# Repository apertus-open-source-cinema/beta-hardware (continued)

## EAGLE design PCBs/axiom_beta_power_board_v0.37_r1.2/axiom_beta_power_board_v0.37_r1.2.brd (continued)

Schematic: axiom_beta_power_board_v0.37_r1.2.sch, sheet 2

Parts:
BETA: µZ-FCI-SOCKET-NOHOLES-R; µZ-SOCKET-NOHOLES-R
FID1, FID2, FID3, FID4: FIDUCIAL; FID_ARROW
JX1T, JX2T: BERGSTAK-61082; 61082

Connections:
BANK13_SE_0: BETA.200 (_0); also elsewhere on the board
CSO_NE_V: BETA.7 (FPGA_VBAT); also elsewhere on the board
CSO_SW_V: BETA.112 (VIN_HDR); also elsewhere on the board
GND: BETA.15 (GND), BETA.16 (GND), BETA.21 (GND), BETA.22 (GND), BETA.27 (GND), BETA.28 (GND), BETA.33 (GND), BETA.34 (GND), BETA.39 (GND), BETA.40 (GND), BETA.45 (GND), BETA.46 (GND), BETA.51 (GND), BETA.52 (GND), BETA.65 (GND), BETA.66 (GND), BETA.71 (GND), BETA.72 (GND), BETA.77 (GND), BETA.85 (GND), BETA.86 (GND), BETA.95 (GND), BETA.96 (GND), BETA.115 (GND), BETA.116 (GND), BETA.121 (GND), BETA.122 (GND), BETA.127 (GND), BETA.128 (GND), BETA.133 (GND), BETA.134 (GND), BETA.139 (GND), BETA.140 (GND), BETA.145 (GND), BETA.146 (GND), BETA.151 (GND), BETA.152 (GND), BETA.165 (GND), BETA.166 (GND), BETA.171 (GND), BETA.172 (GND), BETA.177 (GND), BETA.185 (GND), BETA.186 (GND), BETA.191 (GND), BETA.192 (GND); also elsewhere on the board
NC$1: BETA.113 (_0)
NC$2: BETA.114 (_1)
PCIE_I2C_V: BETA.198 (VCCO_13)
PCIE_N_5V: BETA.59 (VIN_HDR), BETA.60 (VIN_HDR)
PCIE_N_V: BETA.79 (VCCO_34), BETA.80 (VCCO_34); also elsewhere on the board
PCIE_N_VCCIO: BETA.78 (VCCO_34)
PCIE_S_5V: BETA.159 (VIN_HDR), BETA.160 (VIN_HDR)
PCIE_S_V: BETA.179 (VCCO_35), BETA.180 (VCCO_35); also elsewhere on the board
PCIE_S_VCCIO: BETA.178 (VCCO_35)
PEX_N_V: BETA.57 (VIN_HDR), BETA.58 (VIN_HDR)
PEX_S_V: BETA.157 (VIN_HDR), BETA.158 (VIN_HDR)
SE_0: BETA.9 (_0); also elsewhere on the board
SE_1: BETA.10 (_1); also elsewhere on the board

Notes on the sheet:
AXIOM Beta Power Board
Copyright (C) 2014-2020 H.Poetzl Licensed under CERN OHL v.1.2
Beta Main Board Power [Top]

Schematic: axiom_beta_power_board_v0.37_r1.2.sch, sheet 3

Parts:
BETA: µZ-FCI-SOCKET-NOHOLES-R; µZ-SOCKET-NOHOLES-R
C1, C5, C6, C10: 10u; 0603-B
C2, C4, C7, C9: 10u; 1206-C
C3, C8: 1n; 0402-C
C83, C84: 10u; 0603-C
C93: 4u7; 0402-B
D1: PMEG2010BELD; DFN1006D-2
L18: L0603-C; 0603-C
Q1: NX3008NBKT; SOT416
R110: 523k; 0402-C
R111, R115, R118: 100k; 0402-C
R112: 180k; 0402-B
R113: 20k; 0402-B
R114: 536k; 0402-C
R116, R117: 100k; 0402-B
R126: 10k; 0402-B
R127, R129: 180k; 0402-C
R128, R130: 20k; 0402-C
S/N: 91658; 3X2MM
U1: PIC16F15325-JQ; UQFN65P400X400X100-17N
U2, U3: TPS82130SIL-GM; SIL0008D-GM
U26: SC202A; MLPQ-13
U31: NCP715; DFN150X150X50-6N
X2: PINHD-2X02_2.54-90°; 2X02/90
ZED: µZ-FCI-CONONLY; µZ-CONONLY

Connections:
!X_MCLR: R126.2, U1.3 (RA3); also elsewhere on the board
BETA_5V: C4.1, C5.1, D1.A, R110.1, U3.4 (VOUT), U3.5 (VOUT); also elsewhere on the board
BETA_5V': C83.1, U26.5 (CTL3), U26.6 (CTL0), U26.7 (CTL1), U26.8 (CTL2), U26.9 (VIN); also elsewhere on the board
BETA_5V_EN: R116.2, U1.8 (RC1), U3.1 (EN)
BETA_5V_PG: U1.1 (RA5), U3.7 (PG)
BETA_TCK: BETA.1 (TCK)
BETA_TDI: BETA.4 (TDI)
BETA_TDO: BETA.3 (TDO)
BETA_TMS: BETA.2 (TMS)
BTN: R127.1, X2.1
BTN_SENSE: R127.2, R128.1, U1.6 (RC3)
FAN: Q1.3 (D), X2.3
FAN_PWM: R118.2, U1.4 (RC5)
GND: C1.2, C2.2, C3.2, C4.2, C5.2, C6.2, C7.2, C8.2, C9.2, C10.2, C83.2, C84.2, C93.2, Q1.2 (S), R111.2, R113.2, R115.2, R128.2, R130.2, S/N.1, U1.13 (GND), U1.EP (GND), U2.3 (GND), U2.EPAD (GND), U3.3 (GND), U3.EPAD (GND), U26.10 (GND), U31.3 (GND), X2.4; also elsewhere on the board
unnamed: C8.1, U2.8 (SS/TR)
unnamed: C3.1, U3.8 (SS/TR)
unnamed: Q1.1 (G), R118.1
unnamed: R110.2, R111.1, U3.6 (FB)
unnamed: R114.2, R115.1, U2.6 (FB)
REGOUT: C84.1, L18.1, U26.4 (SNS), U26.11 (VOUT), U26.12 (VOUT), U26.13 (VOUT)
SN_SENSE: S/N.2, U1.10 (RA2)
VCC: L18.2, R116.1, R117.1, R129.1; also elsewhere on the board
VCC_SENSE: R129.2, R130.1, U1.7 (RC2)
VIN: C1.1, C2.1, C6.1, C7.1, D1.C (K), R112.1, U2.2 (VIN), U3.2 (VIN), U31.1 (IN), X2.2
VIN_SENSE: R112.2, R113.1, U1.9 (RC0)
VSB: C93.1, R126.1, U1.16 (VCC), U31.6 (OUT); also elsewhere on the board
X_SCL: U1.11 (RA1); also elsewhere on the board
X_SDA: U1.12 (RA0); also elsewhere on the board
ZED_5V: C9.1, C10.1, R114.1, U2.4 (VOUT), U2.5 (VOUT); also elsewhere on the board
ZED_5V_EN: R117.2, U1.5 (RC4), U2.1 (EN)
ZED_5V_PG: U1.2 (RA4), U2.7 (PG)
ZED_TCK: ZED.1 (TCK)
ZED_TDI: ZED.4 (TDI)
ZED_TDO: ZED.3 (TDO)
ZED_TMS: ZED.2 (TMS)

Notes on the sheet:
AXIOM Beta Power Board
Copyright (C) 2014-2020 H.Poetzl Licensed under CERN OHL v.1.2
Power Conversion and JTAG

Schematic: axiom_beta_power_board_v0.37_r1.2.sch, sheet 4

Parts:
BETA: µZ-FCI-SOCKET-NOHOLES-R; µZ-SOCKET-NOHOLES-R
ZED: µZ-FCI-CONONLY; µZ-CONONLY

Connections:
BANK13_00_N: BETA.89 (_N), ZED.89 (_N)
BANK13_00_P: BETA.87 (_P), ZED.87 (_P)
BANK13_01_N: BETA.90 (_N), ZED.90 (_N)
BANK13_01_P: BETA.88 (_P), ZED.88 (_P)
BANK13_02_N: BETA.93 (_N), ZED.93 (_N)
BANK13_02_P: BETA.91 (_P), ZED.91 (_P)
BANK13_03_N: BETA.94 (_N), ZED.94 (_N)
BANK13_03_P: BETA.92 (_P), ZED.92 (_P)
BANK13_04_N: BETA.195 (_N), ZED.195 (_N)
BANK13_04_P: BETA.193 (_P), ZED.193 (_P)
BANK13_05_N: BETA.196 (_N), ZED.196 (_N)
BANK13_05_P: BETA.194 (_P), ZED.194 (_P)
BANK13_06_N: BETA.199 (_N), ZED.199 (_N)
BANK13_06_P: BETA.197 (_P), ZED.197 (_P)
JX1_00_N: BETA.13 (_N), ZED.13 (_N)
JX1_00_P: BETA.11 (_P), ZED.11 (_P)
JX1_01_N: BETA.14 (_N), ZED.14 (_N)
JX1_01_P: BETA.12 (_P), ZED.12 (_P)
JX1_02_N: BETA.19 (_N), ZED.19 (_N)
JX1_02_P: BETA.17 (_P), ZED.17 (_P)
JX1_03_N: BETA.20 (_N), ZED.20 (_N)
JX1_03_P: BETA.18 (_P), ZED.18 (_P)
JX1_04_N: BETA.25 (_N), ZED.25 (_N)
JX1_04_P: BETA.23 (_P), ZED.23 (_P)
JX1_05_N: BETA.26 (_N), ZED.26 (_N)
JX1_05_P: BETA.24 (_P), ZED.24 (_P)
JX1_06_N: BETA.31 (_N), ZED.31 (_N)
JX1_06_P: BETA.29 (_P), ZED.29 (_P)
JX1_07_N: BETA.32 (_N), ZED.32 (_N)
JX1_07_P: BETA.30 (_P), ZED.30 (_P)
JX1_08_N: BETA.37 (_N), ZED.37 (_N)
JX1_08_P: BETA.35 (_P), ZED.35 (_P)
JX1_09_N: BETA.38 (_N), ZED.38 (_N)
JX1_09_P: BETA.36 (_P), ZED.36 (_P)
JX1_10_N: BETA.43 (_N), ZED.43 (_N)
JX1_10_P: BETA.41 (_P), ZED.41 (_P)
JX1_11_N: BETA.44 (_N), ZED.44 (_N)
JX1_11_P: BETA.42 (_P), ZED.42 (_P)
JX1_12_N: BETA.49 (_N), ZED.49 (_N)
JX1_12_P: BETA.47 (_P), ZED.47 (_P)
JX1_13_N: BETA.50 (_N), ZED.50 (_N)
JX1_13_P: BETA.48 (_P), ZED.48 (_P)
JX1_14_N: BETA.55 (_N), ZED.55 (_N)
JX1_14_P: BETA.53 (_P), ZED.53 (_P)
JX1_15_N: BETA.56 (_N), ZED.56 (_N)
JX1_15_P: BETA.54 (_P), ZED.54 (_P)
JX1_16_N: BETA.63 (_N), ZED.63 (_N)
JX1_16_P: BETA.61 (_P), ZED.61 (_P)
JX1_17_N: BETA.64 (_N), ZED.64 (_N)
JX1_17_P: BETA.62 (_P), ZED.62 (_P)
JX1_18_N: BETA.69 (_N), ZED.69 (_N)
JX1_18_P: BETA.67 (_P), ZED.67 (_P)
JX1_19_N: BETA.70 (_N), ZED.70 (_N)
JX1_19_P: BETA.68 (_P), ZED.68 (_P)
JX1_20_N: BETA.75 (_N), ZED.75 (_N)
JX1_20_P: BETA.73 (_P), ZED.73 (_P)
JX1_21_N: BETA.76 (_N), ZED.76 (_N)
JX1_21_P: BETA.74 (_P), ZED.74 (_P)
JX1_22_N: BETA.83 (_N), ZED.83 (_N)
JX1_22_P: BETA.81 (_P), ZED.81 (_P)
JX1_23_N: BETA.84 (_N), ZED.84 (_N)
JX1_23_P: BETA.82 (_P), ZED.82 (_P)
JX2_00_N: BETA.119 (_N), ZED.119 (_N)
JX2_00_P: BETA.117 (_P), ZED.117 (_P)
JX2_01_N: BETA.120 (_N), ZED.120 (_N)
JX2_01_P: BETA.118 (_P), ZED.118 (_P)
JX2_02_N: BETA.125 (_N), ZED.125 (_N)
JX2_02_P: BETA.123 (_P), ZED.123 (_P)
JX2_03_N: BETA.126 (_N), ZED.126 (_N)
JX2_03_P: BETA.124 (_P), ZED.124 (_P)
JX2_04_N: BETA.131 (_N), ZED.131 (_N)
JX2_04_P: BETA.129 (_P), ZED.129 (_P)
JX2_05_N: BETA.132 (_N), ZED.132 (_N)
JX2_05_P: BETA.130 (_P), ZED.130 (_P)
JX2_06_N: BETA.137 (_N), ZED.137 (_N)
JX2_06_P: BETA.135 (_P), ZED.135 (_P)
JX2_07_N: BETA.138 (_N), ZED.138 (_N)
JX2_07_P: BETA.136 (_P), ZED.136 (_P)
JX2_08_N: BETA.143 (_N), ZED.143 (_N)
JX2_08_P: BETA.141 (_P), ZED.141 (_P)
JX2_09_N: BETA.144 (_N), ZED.144 (_N)
JX2_09_P: BETA.142 (_P), ZED.142 (_P)
JX2_10_N: BETA.149 (_N), ZED.149 (_N)
JX2_10_P: BETA.147 (_P), ZED.147 (_P)
JX2_11_N: BETA.150 (_N), ZED.150 (_N)
JX2_11_P: BETA.148 (_P), ZED.148 (_P)
JX2_12_N: BETA.155 (_N), ZED.155 (_N)
JX2_12_P: BETA.153 (_P), ZED.153 (_P)
JX2_13_N: BETA.156 (_N), ZED.156 (_N)
JX2_13_P: BETA.154 (_P), ZED.154 (_P)
JX2_14_N: BETA.163 (_N), ZED.163 (_N)
JX2_14_P: BETA.161 (_P), ZED.161 (_P)
JX2_15_N: BETA.164 (_N), ZED.164 (_N)
JX2_15_P: BETA.162 (_P), ZED.162 (_P)
JX2_16_N: BETA.169 (_N), ZED.169 (_N)
JX2_16_P: BETA.167 (_P), ZED.167 (_P)
JX2_17_N: BETA.170 (_N), ZED.170 (_N)
JX2_17_P: BETA.168 (_P), ZED.168 (_P)
JX2_18_N: BETA.175 (_N), ZED.175 (_N)
JX2_18_P: BETA.173 (_P), ZED.173 (_P)
JX2_19_N: BETA.176 (_N), ZED.176 (_N)
JX2_19_P: BETA.174 (_P), ZED.174 (_P)
JX2_20_N: BETA.183 (_N), ZED.183 (_N)
JX2_20_P: BETA.181 (_P), ZED.181 (_P)
JX2_21_N: BETA.184 (_N), ZED.184 (_N)
JX2_21_P: BETA.182 (_P), ZED.182 (_P)
JX2_22_N: BETA.189 (_N), ZED.189 (_N)
JX2_22_P: BETA.187 (_P), ZED.187 (_P)
JX2_23_N: BETA.190 (_N), ZED.190 (_N)
JX2_23_P: BETA.188 (_P), ZED.188 (_P)

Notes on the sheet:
AXIOM Beta Power Board
Copyright (C) 2014-2020 H.Poetzl Licensed under CERN OHL v.1.2
LVDS Passthrough

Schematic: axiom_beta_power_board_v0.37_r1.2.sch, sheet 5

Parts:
C11, C12, C82, C90: 10n; 0402-B
C91: 1u; 0402-B
C92: 100n; 0402-B
FB1: FB0402-B; 0402-B
PB-NW: DF12(XX)-20DP-0.5V
PB-SE: DF12(XX)-20DP-0.5V
R92, R93, R95, R96, R97, R98, R100, R101, R102, R103, R105, R106, R107, R108, R120, R121: 4k7; 0402-B
R94, R99, R104, R119: 200k; 0402-B
R109: 10k; 0402-B
R122, R123, R124, R125: 50k; 0402-B
SD1: MICRO-SD-2CD; TF-MICRO-SD_PP2
U4, U5, U25, U30: PCA9306GM; PCA9570GMH
U27: TS3A4751; SOP65P640X120-14N
U28: IP4251CZ16-8-TTL; SON40P135X330X55-17N
X1: PICO-SPOX-5
ZED: µZ-FCI-CONONLY; µZ-CONONLY

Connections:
AB_SCL: R93.2, U25.4 (S2); also elsewhere on the board
AB_SCL': R96.2, U25.5 (D2), U27.9 (COM3), U27.10 (COM4), U30.5 (D2)
AB_SDA: R92.2, U25.3 (S1); also elsewhere on the board
AB_SDA': R95.2, U25.6 (D1), U27.2 (COM1), U27.4 (COM2), U30.6 (D1)
A_!RST: PB-NW.1; also elsewhere on the board
A_BUS_EN: U27.12 (EN4), U27.13 (EN1); also elsewhere on the board
A_SCL: PB-NW.2, R101.2, U4.5 (D2)
A_SCL': R98.2, U4.4 (S2), U27.11 (NO4)
A_SDA: PB-NW.4, R100.2, U4.6 (D1)
A_SDA': R97.2, U4.3 (S1), U27.1 (NO1)
BETA_5V: X1.4, X1.4A (4); also elsewhere on the board
B_!RST: PB-SE.1; also elsewhere on the board
B_BUS_EN: U27.5 (EN2), U27.6 (EN3); also elsewhere on the board
B_SCL: PB-SE.2, R106.2, U5.5 (D2)
B_SCL': R103.2, U5.4 (S2), U27.8 (NO3)
B_SDA: PB-SE.4, R105.2, U5.6 (D1)
B_SDA': R102.2, U5.3 (S1), U27.3 (NO2)
CD: SD1.CD1, SD1.CD2, U28.1 (CH1)
CD': R109.2, U28.16 (CH1_2); also elsewhere on the board
CLK: SD1.5, U28.6 (CH6)
CMD: R122.2, SD1.3, U28.5 (CH5)
CTRL: X1.3, X1.3A (3)
DAT0: R123.2, SD1.7, U28.7 (CH7)
DAT1: R124.2, SD1.8, U28.8 (CH8)
DAT2: R125.2, SD1.1, U28.3 (CH3)
DAT3: SD1.2, U28.4 (CH4)
E_VE_CV: PB-SE.20
E_VE_OV: PB-SE.9
E_VE_UV: PB-SE.11
GND: C11.2, C12.2, C82.2, C90.2, C91.2, C92.2, PB-NW.6, PB-SE.6, SD1.6, SD1.MT1 (MT), SD1.MT2 (MT), U4.1 (GND), U5.1 (GND), U25.1 (GND), U27.7 (GND), U28.17 (EP), U30.1 (GND), X1.1, X1.1A (1), X1.5, X1.5A (5); also elsewhere on the board
IOE_V: R104.1, R105.1, R106.1; also elsewhere on the board
IOW_V: R99.1, R100.1, R101.1; also elsewhere on the board
unnamed: C91.1, C92.1, FB1.2, R122.1, R123.1, R124.1, R125.1, SD1.4
unnamed: C90.1, R119.2, U30.7 (DREF), U30.8 (GREF)
unnamed: C11.1, R99.2, U4.7 (DREF), U4.8 (GREF)
unnamed: C12.1, R104.2, U5.7 (DREF), U5.8 (GREF)
unnamed: C82.1, R94.2, U25.7 (DREF), U25.8 (GREF)
N_CHK_V: PB-NW.13
N_VE_CV: PB-NW.18
N_VE_OV: PB-NW.7
N_VE_RS: PB-NW.8
N_VE_UV: PB-NW.19
N_VN_CV: PB-NW.16
N_VN_OV: PB-NW.5
N_VN_RS: PB-NW.12
N_VN_UV: PB-NW.17
N_VW_CV: PB-NW.14
N_VW_OV: PB-NW.3
N_VW_RS: PB-NW.10
N_VW_UV: PB-NW.15
PMOD_D0: U28.9 (CH8_2), ZED.101 (PMOD_D0)
PMOD_D1: U28.10 (CH7_2), ZED.102 (PMOD_D1)
PMOD_D2: U28.12 (CH5_2), ZED.103 (PMOD_D2)
PMOD_D3: U28.11 (CH6_2), ZED.104 (PMOD_D3)
PMOD_D6: U28.14 (CH3_2), ZED.107 (PMOD_D6)
PMOD_D7: U28.13 (CH4_2), ZED.108 (PMOD_D7)
PMOD_SCL: R107.2, ZED.105 (PMOD_D4); also elsewhere on the board
PMOD_SDA: R108.2, ZED.106 (PMOD_D5); also elsewhere on the board
S_CHK_V: PB-SE.13
S_VE_CV: PB-SE.14
S_VE_OV: PB-SE.3
S_VE_RS: PB-SE.10
S_VE_UV: PB-SE.15
S_VS_CV: PB-SE.16
S_VS_OV: PB-SE.5
S_VS_RS: PB-SE.12
S_VS_UV: PB-SE.17
S_VW_CV: PB-SE.18
S_VW_OV: PB-SE.7
S_VW_RS: PB-SE.8
S_VW_UV: PB-SE.19
VCC: FB1.1, R94.1, R95.1, R96.1, R97.1, R98.1, R102.1, R103.1, R107.1, R108.1, R109.1, R119.1, U4.2 (SREF), U5.2 (SREF), U27.14 (VCC); also elsewhere on the board
VCCIO: R92.1, R93.1, U25.2 (SREF); also elsewhere on the board
VSB: R120.1, R121.1, U30.2 (SREF); also elsewhere on the board
W_VW_CV: PB-NW.20
W_VW_OV: PB-NW.9
W_VW_UV: PB-NW.11
X_SCL: R120.2, U30.4 (S2); also elsewhere on the board
X_SDA: R121.2, U30.3 (S1); also elsewhere on the board
ZED_5V: X1.2, X1.2A (2); also elsewhere on the board

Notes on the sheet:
AXIOM Beta Power Board
Copyright (C) 2014-2020 H.Poetzl Licensed under CERN OHL v.1.2
Level Translation and µSD
WUERTH 693071010811 Alternatives (new LP): MOLEX 4735-21001 MEM2051-00-195-00-A

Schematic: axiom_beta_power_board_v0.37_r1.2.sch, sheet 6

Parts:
C64, C67, C70, C73: 4u7; 0603-B
C65, C68, C71, C74: DNP; 0402-B
C66, C69, C72, C75: 10u; 0603-B
C76, C79: 10n; 0402-B
C77, C78, C80, C81: 1u; 0402-B
C89: 100n; 0402-B
CNW: SPX3819M5-L; SOT95P280X145-5N
CSE: SPX3819M5-L; SOT95P280X145-5N
IOE: MCP1727-ADJE/MF; DFN65P300X300X100-9N
IOW: MCP1727-ADJE/MF; DFN65P300X300X100-9N
L14, L15, L16, L17: L0805-B; 0805-B
R43, R45, R47, R49: RB; 0402-B
R44, R46, R48, R50: RD; 0402-B
R63, R64, R65, R66: R1206-B; 1206-B
R79: 5k6; 0402-B
R80: 9k1; 0402-B
RFE: MCP1727-ADJE/MF; DFN65P300X300X100-9N
RFW: MCP1727-ADJE/MF; DFN65P300X300X100-9N
U16, U21: PAC1720; DFN3X3_10LEAD
U29: LM75BGD; SOT996-2/3

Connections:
BETA_5V': C66.1, C69.1, C72.1, C75.1, C78.1, C81.1, CNW.1 (VIN), CSE.1 (VIN), IOE.1 (VIN), IOE.2 (VIN), IOW.1 (VIN), IOW.2 (VIN), RFE.1 (VIN), RFE.2 (VIN), RFW.1 (VIN), RFW.2 (VIN); also elsewhere on the board
CNW_EN: CNW.3 (EN); also elsewhere on the board
CNW_PG: C76.1, CNW.4 (ADJ/BYP); also elsewhere on the board
CSE_EN: CSE.3 (EN); also elsewhere on the board
CSE_PG: C79.1, CSE.4 (ADJ/BYP); also elsewhere on the board
CSO_NW_V: C77.1, CNW.5 (VOUT); also elsewhere on the board
CSO_SE_V: C80.1, CSE.5 (VOUT); also elsewhere on the board
GND: C64.2, C65.2, C66.2, C67.2, C68.2, C69.2, C70.2, C71.2, C72.2, C73.2, C74.2, C75.2, C76.2, C77.2, C78.2, C79.2, C80.2, C81.2, C89.2, CNW.2 (GND), CSE.2 (GND), IOE.4 (GND), IOE.9 (EP), IOW.4 (GND), IOW.9 (EP), R44.2, R46.2, R48.2, R50.2, R79.2, R80.2, RFE.4 (GND), RFE.9 (EP), RFW.4 (GND), RFW.9 (EP), U16.5 (GND), U16.EPAD (GND), U21.5 (GND), U21.EPAD (GND), U29.4 (GND); also elsewhere on the board
IOE_EN: IOE.3 (!SHDN); also elsewhere on the board
IOE_PG: IOE.5 (PWRGD); also elsewhere on the board
IOE_V: R66.2, U21.4 (SENSE2-); also elsewhere on the board
IOE_V': L15.2, R66.1, U21.3 (SENSE2+)
IOW_EN: IOW.3 (!SHDN); also elsewhere on the board
IOW_PG: IOW.5 (PWRGD); also elsewhere on the board
IOW_V: R64.2, U16.4 (SENSE2-); also elsewhere on the board
IOW_V': L17.2, R64.1, U16.3 (SENSE2+)
unnamed: C64.1, L14.1, R47.1, RFE.8 (VOUT)
unnamed: R47.2, R48.1, RFE.7 (ADJ)
unnamed: C65.1, RFE.6 (CDELAY)
unnamed: C67.1, IOE.8 (VOUT), L15.1, R49.1
unnamed: IOE.7 (ADJ), R49.2, R50.1
unnamed: C68.1, IOE.6 (CDELAY)
unnamed: C70.1, L16.1, R43.1, RFW.8 (VOUT)
unnamed: R43.2, R44.1, RFW.7 (ADJ)
unnamed: C71.1, RFW.6 (CDELAY)
unnamed: C73.1, IOW.8 (VOUT), L17.1, R45.1
unnamed: IOW.7 (ADJ), R45.2, R46.1
unnamed: C74.1, IOW.6 (CDELAY)
unnamed: R79.1, U16.6 (ASEL)
unnamed: R80.1, U21.6 (ASEL)
PMOD_SCL: U16.9 (SMCLK), U21.9 (SMCLK), U29.2 (SCL); also elsewhere on the board
PMOD_SDA: U16.8 (SMDATA), U21.8 (SMDATA), U29.1 (SDA); also elsewhere on the board
RFE_EN: RFE.3 (!SHDN); also elsewhere on the board
RFE_PG: RFE.5 (PWRGD); also elsewhere on the board
RFE_V: R65.2, U21.2 (SENSE1-); also elsewhere on the board
RFE_V': L14.2, R65.1, U21.1 (SENSE1+)
RFW_EN: RFW.3 (!SHDN); also elsewhere on the board
RFW_PG: RFW.5 (PWRGD); also elsewhere on the board
RFW_V: R63.2, U16.2 (SENSE1-); also elsewhere on the board
RFW_V': L16.2, R63.1, U16.1 (SENSE1+)
VCC: C89.1, U16.10 (VDD), U21.10 (VDD), U29.5 (A2), U29.6 (A1), U29.7 (A0), U29.8 (VCC); also elsewhere on the board

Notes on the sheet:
AXIOM Beta Power Board
Copyright (C) 2014-2020 H.Poetzl Licensed under CERN OHL v.1.2
Shield Power and Sensing
[0x2C]
[0x2D]
[0x4F]
Temp Sensor
RB RD Voltage 147k,102k ...... 1.001V 68k, 20k ...... 1.804V 102k, 28k ...... 1.904V 124k, 32k ...... 1.999V 85k6, 22k ...... 2.005V 102k, 20k ...... 2.501V 124k, 19k6 .... 3.004V 180k, 25k5 .... 3.304V
[3V3]

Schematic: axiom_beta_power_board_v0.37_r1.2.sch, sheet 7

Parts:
C25, C26, C28, C29, C31, C32, C34, C35: 1u; 0402-B
C27, C30, C33, C36: 4u7; 0603-B
C87, C88: 100n; 0402-B
PWR-NE: PINRC-2X04; R2X04
PWR-NW: PINRC-2X04; R2X04
PWR-SE: PINRC-2X04; R2X04
PWR-SW: PINRC-2X04; R2X04
R84: 22k; 0402-B
R85, R87: 10k; 0402-B
R86: 13k; 0402-B
U8, U9: MCP23018-E/MJ; QFN50P400X400X80-25N
U10, U11, U12, U13: AP7312-3333W6-7; SOT23-6

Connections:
!X_MCLR: U9.24 (GPB0); also elsewhere on the board
A_!RST: U8.19 (GPA4); also elsewhere on the board
A_BUS_EN: U9.6 (GPB6); also elsewhere on the board
BETA_5V': C27.1, C30.1, C33.1, C36.1, U10.5 (VIN), U11.5 (VIN), U12.5 (VIN), U13.5 (VIN); also elsewhere on the board
B_!RST: U9.19 (GPA4); also elsewhere on the board
B_BUS_EN: U9.7 (GPB7); also elsewhere on the board
CD': U9.20 (GPA5); also elsewhere on the board
CNW_EN: U8.22 (GPA7); also elsewhere on the board
CNW_PG: U8.21 (GPA6); also elsewhere on the board
CSE_EN: U9.22 (GPA7); also elsewhere on the board
CSE_PG: U9.21 (GPA6); also elsewhere on the board
CSO_NW_V: PWR-NW.6; also elsewhere on the board
CSO_SE_V: PWR-SE.6; also elsewhere on the board
E_I2C_EN: U9.5 (GPB5), U12.3 (EN2)
E_I2C_V: C31.1, PWR-NE.6, U12.1 (VOUT2)
E_SPI_EN: U9.2 (GPB2), U12.4 (EN1)
E_SPI_V: C32.1, PWR-NE.8, U12.6 (VOUT1)
E_VE: PWR-SE.4; also elsewhere on the board
GND: C25.2, C26.2, C27.2, C28.2, C29.2, C30.2, C31.2, C32.2, C33.2, C34.2, C35.2, C36.2, C87.2, C88.2, PWR-NE.2, PWR-NE.4, PWR-NW.1, PWR-NW.3, PWR-SE.1, PWR-SE.3, PWR-SW.2, PWR-SW.4, R85.2, R87.2, U8.23 (VSS), U8.25 (VSS), U9.23 (VSS), U9.25 (VSS), U10.2 (GND), U11.2 (GND), U12.2 (GND), U13.2 (GND); also elsewhere on the board
IOE_EN: U9.16 (GPA1); also elsewhere on the board
IOE_PG: U9.15 (GPA0); also elsewhere on the board
IOE_V: PWR-SE.5; also elsewhere on the board
IOW_EN: U8.16 (GPA1); also elsewhere on the board
IOW_PG: U8.15 (GPA0); also elsewhere on the board
IOW_V: PWR-NW.5; also elsewhere on the board
JTAG_EN: U8.2 (GPB2), U10.4 (EN1)
JTAG_V: C26.1, PWR-SW.8, U10.6 (VOUT1)
unnamed: R84.2, R85.1, U9.11 (ADDR)
unnamed: R86.2, R87.1, U8.11 (ADDR)
N_I2C_EN: U9.3 (GPB3), U13.4 (EN1)
N_I2C_V: C35.1, PWR-NE.7, U13.6 (VOUT1)
N_SPI_EN: U9.4 (GPB4), U13.3 (EN2)
N_SPI_V: C34.1, PWR-NE.5, U13.1 (VOUT2)
N_VE: PWR-NE.3; also elsewhere on the board
N_VN: PWR-NE.1; also elsewhere on the board
N_VW: PWR-NW.2; also elsewhere on the board
PMOD_SCL: U8.9 (SCL), U9.9 (SCL); also elsewhere on the board
PMOD_SDA: U8.10 (SDA), U9.10 (SDA); also elsewhere on the board
RFAB_E_V: PWR-SE.8
RFAB_W_V: PWR-NW.8
RFE_EN: U9.18 (GPA3); also elsewhere on the board
RFE_PG: U9.17 (GPA2); also elsewhere on the board
RFE_V: PWR-SE.7; also elsewhere on the board
RFW_EN: U8.18 (GPA3); also elsewhere on the board
RFW_PG: U8.17 (GPA2); also elsewhere on the board
RFW_V: PWR-NW.7; also elsewhere on the board
S_I2C_EN: U8.3 (GPB3), U11.4 (EN1)
S_I2C_V: C29.1, PWR-SW.7, U11.6 (VOUT1)
S_SPI_EN: U8.4 (GPB4), U11.3 (EN2)
S_SPI_V: C28.1, PWR-SW.5, U11.1 (VOUT2)
S_VE: PWR-SE.2; also elsewhere on the board
S_VS: PWR-SW.1; also elsewhere on the board
S_VW: PWR-SW.3; also elsewhere on the board
VCC: C87.1, C88.1, R84.1, R86.1, U8.8 (VDD), U8.12 (!RESET), U9.8 (VDD), U9.12 (!RESET); also elsewhere on the board
W_I2C_EN: U8.5 (GPB5), U10.3 (EN2)
W_I2C_V: C25.1, PWR-SW.6, U10.1 (VOUT2)
W_VW: PWR-NW.4; also elsewhere on the board

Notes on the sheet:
AXIOM Beta Power Board
Copyright (C) 2014-2020 H.Poetzl Licensed under CERN OHL v.1.2
Interface Power and Control
[ID=0x22]
[ID=0x23]

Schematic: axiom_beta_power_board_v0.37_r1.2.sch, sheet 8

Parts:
C13, C16, C19, C22, C37, C40, C43, C46: 4u7; 0603-B
C14, C17, C20, C23, C38, C41, C44, C47: DNP; 0402-B
C15, C18, C21, C24, C39, C42, C45, C48: 10u; 0603-B
C85: 100n; 0402-B
EE: MCP1727-ADJE/MF; DFN65P300X300X100-9N
L1, L2, L3, L4, L5, L6, L7, L8: L0805-B; 0805-B
NE: MCP1727-ADJE/MF; DFN65P300X300X100-9N
NN: MCP1727-ADJE/MF; DFN65P300X300X100-9N
NW: MCP1727-ADJE/MF; DFN65P300X300X100-9N
R1, R5, R9, R13, R17, R21, R25, R29: RA; 0402-B
R2, R6, R10, R14, R18, R22, R26, R30: RB; 0402-B
R3, R7, R11, R15, R19, R23, R27, R31: RC; 0402-B
R4, R8, R12, R16, R20, R24, R28, R32: RD; 0402-B
R88: 13k; 0402-B
R89: 3k; 0402-B
SE: MCP1727-ADJE/MF; DFN65P300X300X100-9N
SS: MCP1727-ADJE/MF; DFN65P300X300X100-9N
SW: MCP1727-ADJE/MF; DFN65P300X300X100-9N
TR1, TR2, TR3, TR4, TR5, TR6, TR7, TR8: PVZ2A; TRIM-PVZ2A
U6: MCP23018-E/MJ; QFN50P400X400X80-25N
WW: MCP1727-ADJE/MF; DFN65P300X300X100-9N

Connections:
BETA_5V': C15.1, C18.1, C21.1, C24.1, C39.1, C42.1, C45.1, C48.1, EE.1 (VIN), EE.2 (VIN), NE.1 (VIN), NE.2 (VIN), NN.1 (VIN), NN.2 (VIN), NW.1 (VIN), NW.2 (VIN), SE.1 (VIN), SE.2 (VIN), SS.1 (VIN), SS.2 (VIN), SW.1 (VIN), SW.2 (VIN), WW.1 (VIN), WW.2 (VIN); also elsewhere on the board
EE_EN: EE.3 (!SHDN), U6.7 (GPB7)
EE_PG: EE.5 (PWRGD), U6.6 (GPB6)
E_VE': L5.2; also elsewhere on the board
GND: C13.2, C14.2, C15.2, C16.2, C17.2, C18.2, C19.2, C20.2, C21.2, C22.2, C23.2, C24.2, C37.2, C38.2, C39.2, C40.2, C41.2, C42.2, C43.2, C44.2, C45.2, C46.2, C47.2, C48.2, C85.2, EE.4 (GND), EE.9 (EP), NE.4 (GND), NE.9 (EP), NN.4 (GND), NN.9 (EP), NW.4 (GND), NW.9 (EP), R3.2, R4.2, R7.2, R8.2, R11.2, R12.2, R15.2, R16.2, R19.2, R20.2, R23.2, R24.2, R27.2, R28.2, R31.2, R32.2, R89.2, SE.4 (GND), SE.9 (EP), SS.4 (GND), SS.9 (EP), SW.4 (GND), SW.9 (EP), U6.23 (VSS), U6.25 (VSS), WW.4 (GND), WW.9 (EP); also elsewhere on the board
unnamed: C13.1, L1.1, R1.2, R2.1, WW.8 (VOUT)
unnamed: R2.2, R4.1, TR1.2 (B), WW.7 (ADJ)
unnamed: R3.1, TR1.1 (A)
unnamed: C14.1, WW.6 (CDELAY)
unnamed: R1.1, TR1.3 (C)
unnamed: C16.1, L2.1, NW.8 (VOUT), R5.2, R6.1
unnamed: NW.7 (ADJ), R6.2, R8.1, TR2.2 (B)
unnamed: R7.1, TR2.1 (A)
unnamed: C17.1, NW.6 (CDELAY)
unnamed: C19.1, L3.1, NN.8 (VOUT), R9.2, R10.1
unnamed: NN.7 (ADJ), R10.2, R12.1, TR3.2 (B)
unnamed: R5.1, TR2.3 (C)
unnamed: C20.1, NN.6 (CDELAY)
unnamed: C22.1, L4.1, NE.8 (VOUT), R13.2, R14.1
unnamed: NE.7 (ADJ), R14.2, R16.1, TR4.2 (B)
unnamed: R11.1, TR3.1 (A)
unnamed: C23.1, NE.6 (CDELAY)
unnamed: C37.1, EE.8 (VOUT), L5.1, R17.2, R18.1
unnamed: EE.7 (ADJ), R18.2, R20.1, TR5.2 (B)
unnamed: R9.1, TR3.3 (C)
unnamed: C38.1, EE.6 (CDELAY)
unnamed: R15.1, TR4.1 (A)
unnamed: C40.1, L6.1, R21.2, R22.1, SE.8 (VOUT)
unnamed: R22.2, R24.1, SE.7 (ADJ), TR6.2 (B)
unnamed: R13.1, TR4.3 (C)
unnamed: C41.1, SE.6 (CDELAY)
unnamed: R19.1, TR5.1 (A)
unnamed: C43.1, L7.1, R25.2, R26.1, SS.8 (VOUT)
unnamed: R26.2, R28.1, SS.7 (ADJ), TR7.2 (B)
unnamed: R17.1, TR5.3 (C)
unnamed: C44.1, SS.6 (CDELAY)
unnamed: R23.1, TR6.1 (A)
unnamed: C46.1, L8.1, R29.2, R30.1, SW.8 (VOUT)
unnamed: R30.2, R32.1, SW.7 (ADJ), TR8.2 (B)
unnamed: R21.1, TR6.3 (C)
unnamed: C47.1, SW.6 (CDELAY)
unnamed: R27.1, TR7.1 (A)
unnamed: R25.1, TR7.3 (C)
unnamed: R31.1, TR8.1 (A)
unnamed: R29.1, TR8.3 (C)
unnamed: R88.2, R89.1, U6.11 (ADDR)
NE_EN: NE.3 (!SHDN), U6.16 (GPA1)
NE_PG: NE.5 (PWRGD), U6.15 (GPA0)
NN_EN: NN.3 (!SHDN), U6.18 (GPA3)
NN_PG: NN.5 (PWRGD), U6.17 (GPA2)
NW_EN: NW.3 (!SHDN), U6.20 (GPA5)
NW_PG: NW.5 (PWRGD), U6.19 (GPA4)
N_VE': L4.2; also elsewhere on the board
N_VN': L3.2; also elsewhere on the board
N_VW': L2.2; also elsewhere on the board
PMOD_SCL: U6.9 (SCL); also elsewhere on the board
PMOD_SDA: U6.10 (SDA); also elsewhere on the board
SE_EN: SE.3 (!SHDN), U6.5 (GPB5)
SE_PG: SE.5 (PWRGD), U6.4 (GPB4)
SS_EN: SS.3 (!SHDN), U6.3 (GPB3)
SS_PG: SS.5 (PWRGD), U6.2 (GPB2)
SW_EN: SW.3 (!SHDN), U6.1 (GPB1)
SW_PG: SW.5 (PWRGD), U6.24 (GPB0)
S_VE': L6.2; also elsewhere on the board
S_VS': L7.2; also elsewhere on the board
S_VW': L8.2; also elsewhere on the board
VCC: C85.1, R88.1, U6.8 (VDD), U6.12 (!RESET); also elsewhere on the board
WW_EN: U6.22 (GPA7), WW.3 (!SHDN)
WW_PG: U6.21 (GPA6), WW.5 (PWRGD)
W_VW': L1.2; also elsewhere on the board

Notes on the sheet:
AXIOM Beta Power Board
Copyright (C) 2014-2020 H.Poetzl Licensed under CERN OHL v.1.2
Sensor Power and Control
[ID=0x21]
RD Trim RA Nom. Range 18k, 100k, 43k ...... 1.389V - 3.667V 20k, 100k, 62k ...... 1.681V - 3.731V 20k5, 100k, 68k ...... 1.770V - 3.770V 13k, 75k, 30k9 .... 1.385V - 3.750V 12k4, 75k, 30k ...... 1.402V - 3.882V
Optional remote sensing
RA RB RC RD Trim Nom. Range 180k, 430k, 20k, 180k, 47k ...... 1.475V - 3.794V 240k, 240k, 18k, 160k, 47k ...... 1.474V - 3.722V 147k, 255k, 14k3, 143k, 47k ...... 1.301V - 3.885V 390k, 360k, 30k, 160k, 100k ...... 1.480V - 3.778V 309k, 365k, 26k1, 191k, 100k ...... 1.313V - 3.854V 324k, 432k, 30k1,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
[2V5]
[3V3]
[1V9]
[1V0]
[3V0]

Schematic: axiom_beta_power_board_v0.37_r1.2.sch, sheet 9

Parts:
R51, R52, R53, R54, R55, R56, R57, R58, R59, R60, R61, R62: R1206-B; 1206-B
R73: 750R; 0402-B
R74: 1k27; 0402-B
R75: 430R; 0402-B
R76: 0R; 0402-B
R77: 100R; 0402-B
R78: 560R; 0402-B
U17, U18, U19, U20, U23, U24: PAC1720; DFN3X3_10LEAD

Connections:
E_VE: R57.2, U19.2 (SENSE1-); also elsewhere on the board
E_VE': R57.1, U19.1 (SENSE1+); also elsewhere on the board
GND: R73.2, R74.2, R75.2, R76.2, R77.2, R78.2, U17.5 (GND), U17.EPAD (GND), U18.5 (GND), U18.EPAD (GND), U19.5 (GND), U19.EPAD (GND), U20.5 (GND), U20.EPAD (GND), U23.5 (GND), U23.EPAD (GND), U24.5 (GND), U24.EPAD (GND); also elsewhere on the board
unnamed: R73.1, U18.6 (ASEL)
unnamed: R75.1, U24.6 (ASEL)
unnamed: R78.1, U23.6 (ASEL)
unnamed: R74.1, U20.6 (ASEL)
unnamed: R76.1, U19.6 (ASEL)
unnamed: R77.1, U17.6 (ASEL)
N_VE: R54.2, U20.4 (SENSE2-); also elsewhere on the board
N_VE': R54.1, U20.3 (SENSE2+); also elsewhere on the board
N_VN: R53.2, U20.2 (SENSE1-); also elsewhere on the board
N_VN': R53.1, U20.1 (SENSE1+); also elsewhere on the board
N_VW: R52.2, U18.4 (SENSE2-); also elsewhere on the board
N_VW': R52.1, U18.3 (SENSE2+); also elsewhere on the board
PCIE_VCCIO: R61.2, U23.2 (SENSE1-)
PMOD_SCL: U17.9 (SMCLK), U18.9 (SMCLK), U19.9 (SMCLK), U20.9 (SMCLK), U23.9 (SMCLK), U24.9 (SMCLK); also elsewhere on the board
PMOD_SDA: U17.8 (SMDATA), U18.8 (SMDATA), U19.8 (SMDATA), U20.8 (SMDATA), U23.8 (SMDATA), U24.8 (SMDATA); also elsewhere on the board
S_VE: R58.2, U19.4 (SENSE2-); also elsewhere on the board
S_VE': R58.1, U19.3 (SENSE2+); also elsewhere on the board
S_VS: R59.2, U17.2 (SENSE1-); also elsewhere on the board
S_VS': R59.1, U17.1 (SENSE1+); also elsewhere on the board
S_VW: R60.2, U17.4 (SENSE2-); also elsewhere on the board
S_VW': R60.1, U17.3 (SENSE2+); also elsewhere on the board
VCC: U17.10 (VDD), U18.10 (VDD), U19.10 (VDD), U20.10 (VDD), U23.10 (VDD), U24.10 (VDD); also elsewhere on the board
VCCIO: R55.1, R56.1, R61.1, R62.1, U23.1 (SENSE1+), U23.3 (SENSE2+), U24.1 (SENSE1+), U24.3 (SENSE2+); also elsewhere on the board
VCCO_13: R56.2, U24.4 (SENSE2-); also elsewhere on the board
VCCO_34: R62.2, U23.4 (SENSE2-); also elsewhere on the board
VCCO_35: R55.2, U24.2 (SENSE1-); also elsewhere on the board
W_VW: R51.2, U18.2 (SENSE1-); also elsewhere on the board
W_VW': R51.1, U18.1 (SENSE1+); also elsewhere on the board

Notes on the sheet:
AXIOM Beta Power Board
Copyright (C) 2014-2020 H.Poetzl Licensed under CERN OHL v.1.2
Sensor Power Sensing
[0x48]
[0x49]
[0x4B]
[0x4D]
[0x4A]
[0x4C]

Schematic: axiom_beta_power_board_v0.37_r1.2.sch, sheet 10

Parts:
C49, C52, C55, C58, C61: 4u7; 0603-B
C50, C53, C56, C59, C62: DNP; 0402-B
C51, C54, C57, C60, C63: 10u; 0603-B
C86: 100n; 0402-B
L9, L10, L11, L12, L13: L0805-A; 0805-A
MCN: MCP1727-ADJE/MF; DFN65P300X300X100-9N
MCS: MCP1727-ADJE/MF; DFN65P300X300X100-9N
MXN: MCP1727-ADJE/MF; DFN65P300X300X100-9N
MXS: MCP1727-ADJE/MF; DFN65P300X300X100-9N
R33, R35, R39, R41: RB; 0402-B
R34, R36, R40, R42: RD; 0402-B
R37: 102k; 0402-B
R38: 20k; 0402-B
R67, R68, R69, R70, R71, R72: R1206-B; 1206-B
R81: 2k0; 0402-B
R82: 1k6; 0402-B
R83: 2k7; 0402-B
R90: 15k; 0402-B
R91: 1k; 0402-B
U7: MCP23018-E/MJ; QFN50P400X400X80-25N
U14, U15, U22: PAC1720; DFN3X3_10LEAD
VIO: MCP1727-ADJE/MF; DFN65P300X300X100-9N

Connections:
BETA_5V: R70.1, U22.3 (SENSE2+); also elsewhere on the board
BETA_5V': C51.1, C54.1, C57.1, C60.1, C63.1, MCN.1 (VIN), MCN.2 (VIN), MCS.1 (VIN), MCS.2 (VIN), MXN.1 (VIN), MXN.2 (VIN), MXS.1 (VIN), MXS.2 (VIN), R70.2, U22.4 (SENSE2-), VIO.1 (VIN), VIO.2 (VIN); also elsewhere on the board
CSO_NE_V: R67.2, U14.2 (SENSE1-); also elsewhere on the board
CSO_N_V': L12.2, R67.1, U14.1 (SENSE1+)
CSO_SW_V: R71.2, U15.2 (SENSE1-); also elsewhere on the board
CSO_S_V': L10.2, R71.1, U15.1 (SENSE1+)
GND: C49.2, C50.2, C51.2, C52.2, C53.2, C54.2, C55.2, C56.2, C57.2, C58.2, C59.2, C60.2, C61.2, C62.2, C63.2, C86.2, MCN.4 (GND), MCN.9 (EP), MCS.4 (GND), MCS.9 (EP), MXN.4 (GND), MXN.9 (EP), MXS.4 (GND), MXS.9 (EP), R34.2, R36.2, R38.2, R40.2, R42.2, R81.2, R82.2, R83.2, R91.2, U7.23 (VSS), U7.25 (VSS), U14.5 (GND), U14.EPAD (GND), U15.5 (GND), U15.EPAD (GND), U22.5 (GND), U22.EPAD (GND), VIO.4 (GND), VIO.9 (EP); also elsewhere on the board
MCN_EN: MCN.3 (!SHDN), U7.18 (GPA3)
MCN_PG: MCN.5 (PWRGD), U7.17 (GPA2)
MCS_EN: MCS.3 (!SHDN), U7.22 (GPA7)
MCS_PG: MCS.5 (PWRGD), U7.21 (GPA6)
MXN_EN: MXN.3 (!SHDN), U7.16 (GPA1)
MXN_PG: MXN.5 (PWRGD), U7.15 (GPA0)
MXS_EN: MXS.3 (!SHDN), U7.1 (GPB1)
MXS_PG: MXS.5 (PWRGD), U7.24 (GPB0)
unnamed: C49.1, L9.1, MXS.8 (VOUT), R41.1
unnamed: MXS.7 (ADJ), R41.2, R42.1
unnamed: C50.1, MXS.6 (CDELAY)
unnamed: R81.1, U14.6 (ASEL)
unnamed: R83.1, U15.6 (ASEL)
unnamed: C52.1, L10.1, MCS.8 (VOUT), R39.1
unnamed: MCS.7 (ADJ), R39.2, R40.1
unnamed: C53.1, MCS.6 (CDELAY)
unnamed: R82.1, U22.6 (ASEL)
unnamed: C55.1, L11.1, R37.1, VIO.8 (VOUT)
unnamed: R37.2, R38.1, VIO.7 (ADJ)
unnamed: C56.1, VIO.6 (CDELAY)
unnamed: C58.1, L12.1, MCN.8 (VOUT), R35.1
unnamed: MCN.7 (ADJ), R35.2, R36.1
unnamed: C59.1, MCN.6 (CDELAY)
unnamed: C61.1, L13.1, MXN.8 (VOUT), R33.1
unnamed: MXN.7 (ADJ), R33.2, R34.1
unnamed: C62.1, MXN.6 (CDELAY)
unnamed: R90.2, R91.1, U7.11 (ADDR)
PCIE_N_V: R68.2, U14.4 (SENSE2-); also elsewhere on the board
PCIE_N_V': L13.2, R68.1, U14.3 (SENSE2+)
PCIE_S_V: R72.2, U15.4 (SENSE2-); also elsewhere on the board
PCIE_S_V': L9.2, R72.1, U15.3 (SENSE2+)
PMOD_SCL: U7.9 (SCL), U14.9 (SMCLK), U15.9 (SMCLK), U22.9 (SMCLK); also elsewhere on the board
PMOD_SDA: U7.10 (SDA), U14.8 (SMDATA), U15.8 (SMDATA), U22.8 (SMDATA); also elsewhere on the board
VCC: C86.1, R90.1, U7.8 (VDD), U7.12 (!RESET), U14.10 (VDD), U15.10 (VDD), U22.10 (VDD); also elsewhere on the board
VCCIO: L11.2; also elsewhere on the board
VIO_EN: U7.20 (GPA5), VIO.3 (!SHDN)
VIO_PG: U7.19 (GPA4), VIO.5 (PWRGD)
ZED_5V: R69.1, U22.1 (SENSE1+); also elsewhere on the board
ZED_5V': R69.2, U22.2 (SENSE1-); also elsewhere on the board

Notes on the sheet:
AXIOM Beta Power Board
Copyright (C) 2014-2020 H.Poetzl Licensed under CERN OHL v.1.2
Power, Control and Sensing
[ID=0x20]
[0x29]
[0x28]
[0x2A]
[3V3]
[2V5]

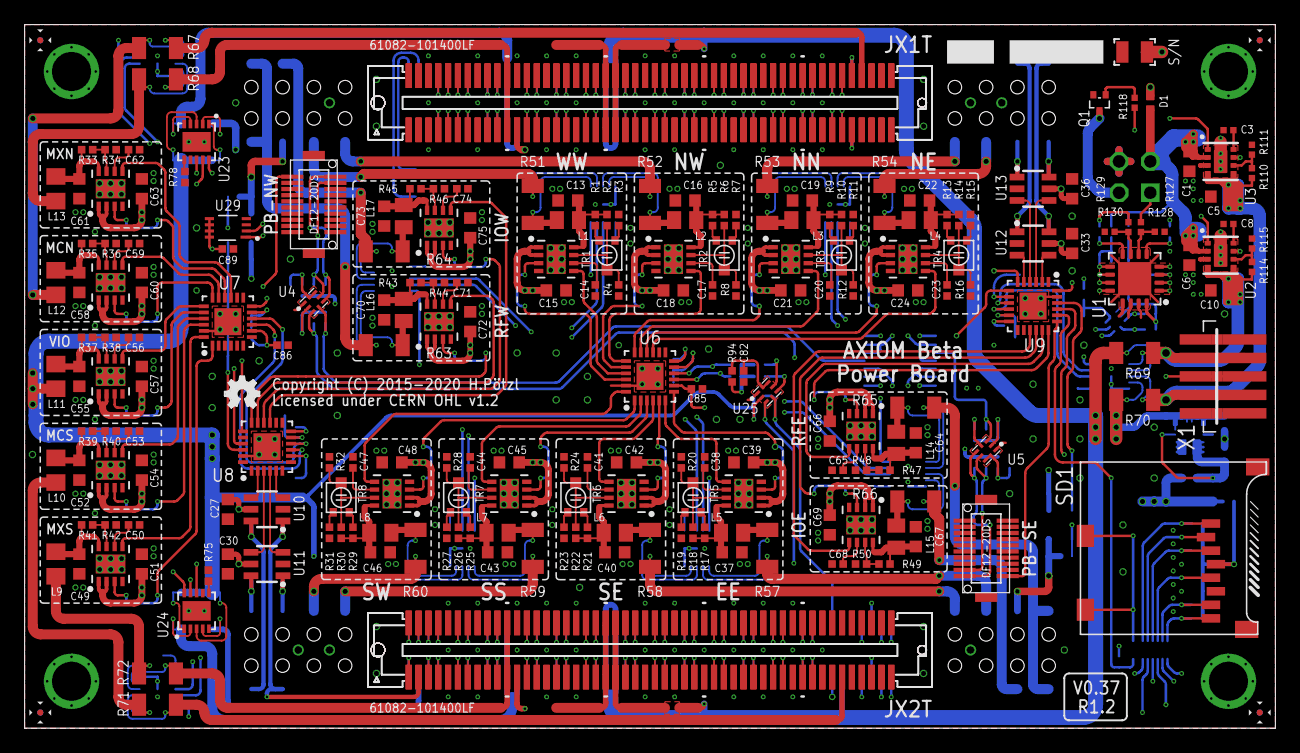
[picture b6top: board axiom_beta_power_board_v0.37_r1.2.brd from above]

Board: 4 copper layers, 101.6 x 57.1 mm, 329 parts (110 on the bottom side), 360 nets.

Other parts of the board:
LOGO1: OSHW_LOGO_FILLX0100-NT; OSHW_FILLX100_NOTEXT

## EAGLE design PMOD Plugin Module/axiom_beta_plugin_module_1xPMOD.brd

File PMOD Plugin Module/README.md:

# AXIOM Beta PMOD Plugin Modules

## 1x PMOD v0.1

https://wiki.apertus.org/index.php/Beta_1x_PMOD_Plugin_Module

## 3x PMOD v1.2

https://wiki.apertus.org/index.php/Beta_3x_PMOD_Plugin_Module

BOM: https://octopart.com/bom-tool/sKUjCtfB

## PMOD LED Matrix

https://wiki.apertus.org/index.php/PMOD_LED_Matrix_Debug_Module

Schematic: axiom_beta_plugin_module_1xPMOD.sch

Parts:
C1: 100n; 0402-B
C2: 100u; 1206-A
LED0, LED1, LED2, LED3, LED4, LED5, LED6, LED7, LED8: LEDCHIPLED_0603; CHIPLED_0603
PCIE-UNSPEC: PCIE-36-AXIOM
PMOD1-1, PMOD1-2, PMOD1-3, PMOD1-4, PMOD1-5, PMOD1-6, PMOD1-7, PMOD1-8, PMOD1-9, PMOD1-10, PMOD1-11, PMOD1-12, PMOD2-1, PMOD2-2, PMOD2-3, PMOD2-4, PMOD2-5, PMOD2-6: SMD-PAD1.6X3.8MM-U; 1.6X3.8U-MM
R1, R3: 10k; 0402-B
R2: 1k; 0402-B
RN1, RN2: 10k; CAY16
U1: BR24G04NUX; DFN200X300X100-9N

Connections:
GND: C1.2, C2.2, LED0.C, LED1.C, LED2.C, LED3.C, LED4.C, LED5.C, LED6.C, LED7.C, LED8.C, PCIE-UNSPEC.A1 (GND), PCIE-UNSPEC.A4 (GND), PCIE-UNSPEC.A7 (GND), PCIE-UNSPEC.A10 (GND), PCIE-UNSPEC.A12 (GND), PCIE-UNSPEC.A15 (GND), PCIE-UNSPEC.A18 (GND), PCIE-UNSPEC.B15 (GND), PCIE-UNSPEC.B18 (GND), PMOD1-5.1, PMOD1-11.1, PMOD2-3.1, PMOD2-6.1, R2.2, U1.1 (A0), U1.2 (A1), U1.3 (A2), U1.4 (GND), U1.EP
I2C_V: C1.1, PCIE-UNSPEC.B3 (V_I2C), R1.1, U1.8 (VCC)
IO0: PCIE-UNSPEC.B4 (IO0), RN1.5 (2)
IO1: PCIE-UNSPEC.B5 (IO1), RN1.6 (2)
IO2: PCIE-UNSPEC.B6 (IO2), RN1.7 (2)
IO3: PCIE-UNSPEC.B7 (IO3), RN1.8 (2)
IO4: PCIE-UNSPEC.B8 (IO4), RN2.5 (2)
IO5: PCIE-UNSPEC.B9 (IO5), RN2.6 (2)
IO6: PCIE-UNSPEC.B10 (IO6), RN2.7 (2)
IO7: PCIE-UNSPEC.B11 (IO7), RN2.8 (2)
LVDS_0_N: PCIE-UNSPEC.A3 (LVDS_0B), PMOD2-2.1
LVDS_0_P: PCIE-UNSPEC.A2 (LVDS_0A), PMOD2-5.1
LVDS_1_N: PCIE-UNSPEC.A6 (LVDS_1B), PMOD2-1.1
LVDS_1_P: PCIE-UNSPEC.A5 (LVDS_1A), PMOD2-4.1
LVDS_2_N: PCIE-UNSPEC.A9 (LVDS_2B), PMOD1-1.1
LVDS_2_P: PCIE-UNSPEC.A8 (LVDS_2A), PMOD1-7.1
LVDS_3_N: PCIE-UNSPEC.A14 (LVDS_3B), PMOD1-2.1
LVDS_3_P: PCIE-UNSPEC.A13 (LVDS_3A), PMOD1-8.1
LVDS_4_N: PCIE-UNSPEC.A17 (LVDS_4B), PMOD1-3.1
LVDS_4_P: PCIE-UNSPEC.A16 (LVDS_4A), PMOD1-9.1
LVDS_5_N: PCIE-UNSPEC.B17 (LVDS_5B), PMOD1-4.1
LVDS_5_P: PCIE-UNSPEC.B16 (LVDS_5A), PMOD1-10.1
unnamed: R1.2, R2.1, U1.7 (WP)
unnamed: LED3.A, RN1.1
unnamed: LED2.A, RN1.2 (1)
unnamed: LED1.A, RN1.3 (1)
unnamed: LED0.A, RN1.4 (1)
unnamed: LED8.A, R3.2
unnamed: LED7.A, RN2.1
unnamed: LED6.A, RN2.2 (1)
unnamed: LED5.A, RN2.3 (1)
unnamed: LED4.A, RN2.4 (1)
PCIE_5V: PCIE-UNSPEC.B12 (5V)
PCIE_VCC: C2.1, PCIE-UNSPEC.B13 (VCC), PMOD1-6.1, PMOD1-12.1, R3.1
PCIE_VCCIO: PCIE-UNSPEC.B14 (VCCIO)
SCL: PCIE-UNSPEC.B2 (SCL), U1.6 (SCL)
SDA: PCIE-UNSPEC.B1 (SDA), U1.5 (SDA)

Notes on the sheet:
AXIOM Beta Module
Copyright (C) 2015 H.Poetzl Licensed under CERN OHL v.1.2
Single HDMI Single Module
Info EEPROM
Use XX for CEC/HEAC?
Full PMOD
Half PMOD

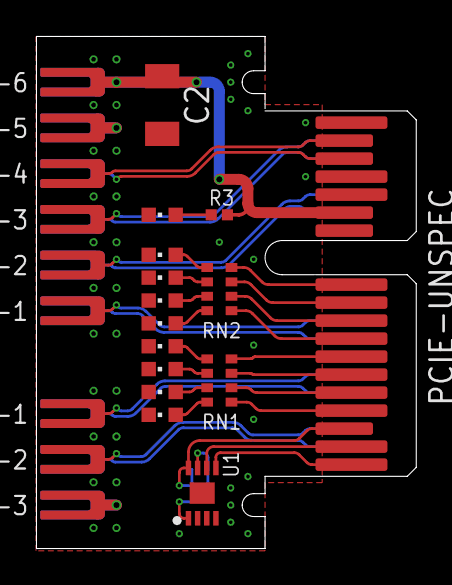
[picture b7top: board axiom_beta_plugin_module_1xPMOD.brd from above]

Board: 4 copper layers, 21.1 x 28.4 mm, 38 parts (13 on the bottom side), 35 nets.

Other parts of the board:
LOGO1, LOGO2: OSHW_LOGO_FILLX0100-NT; OSHW_FILLX100_NOTEXT
